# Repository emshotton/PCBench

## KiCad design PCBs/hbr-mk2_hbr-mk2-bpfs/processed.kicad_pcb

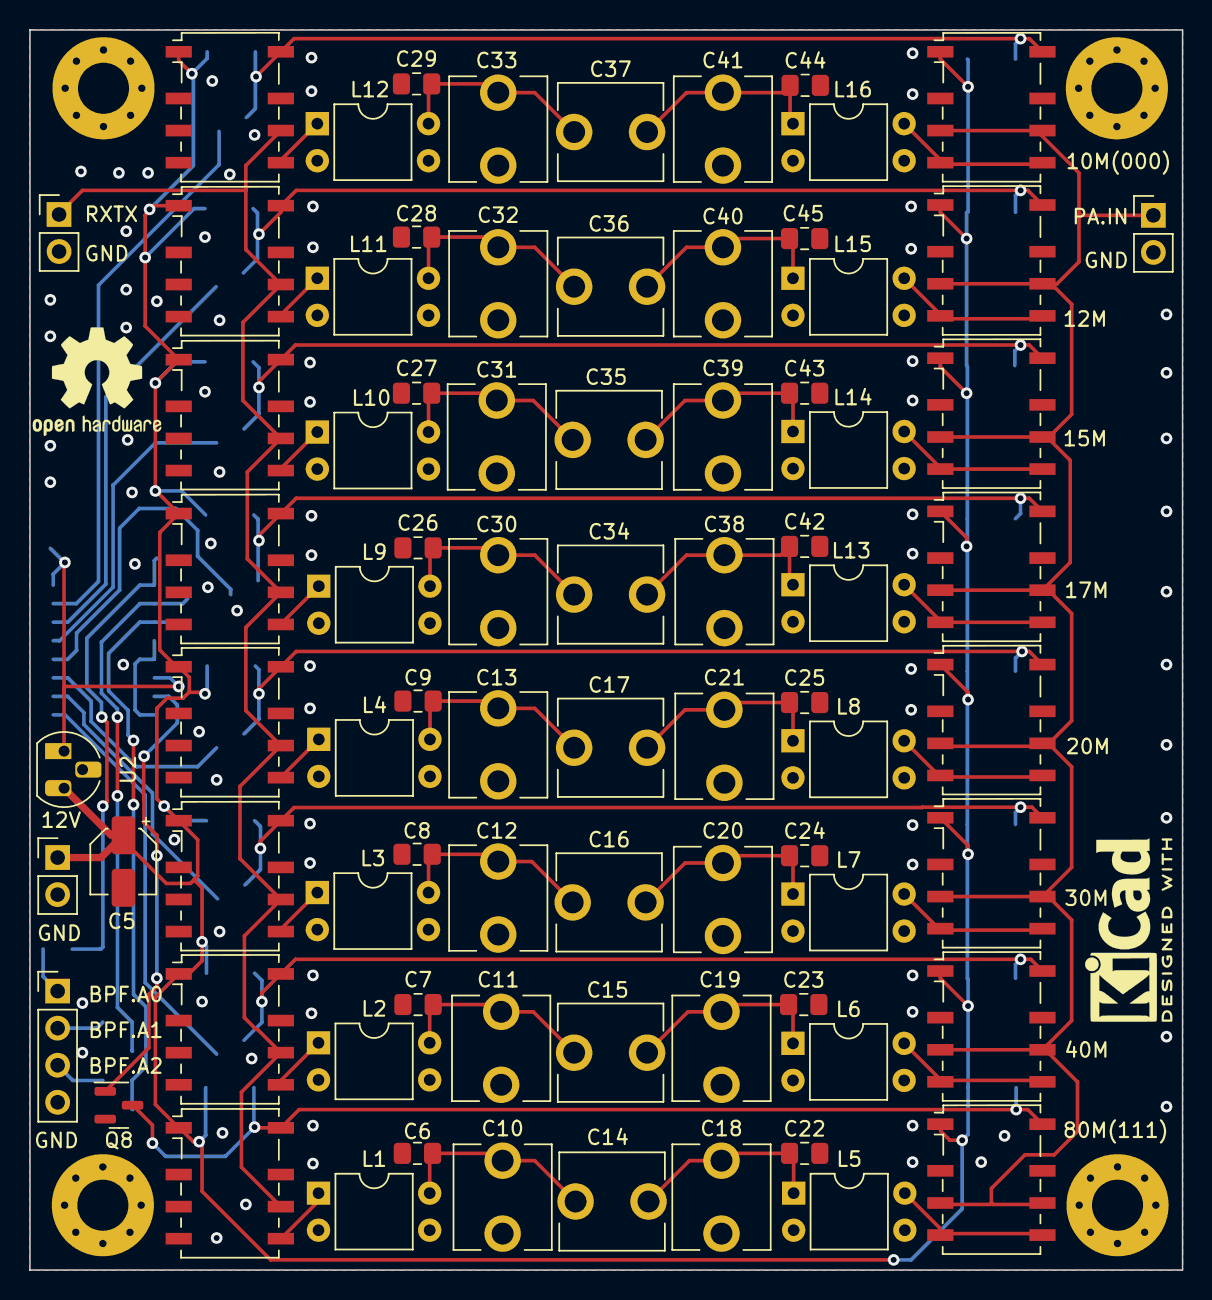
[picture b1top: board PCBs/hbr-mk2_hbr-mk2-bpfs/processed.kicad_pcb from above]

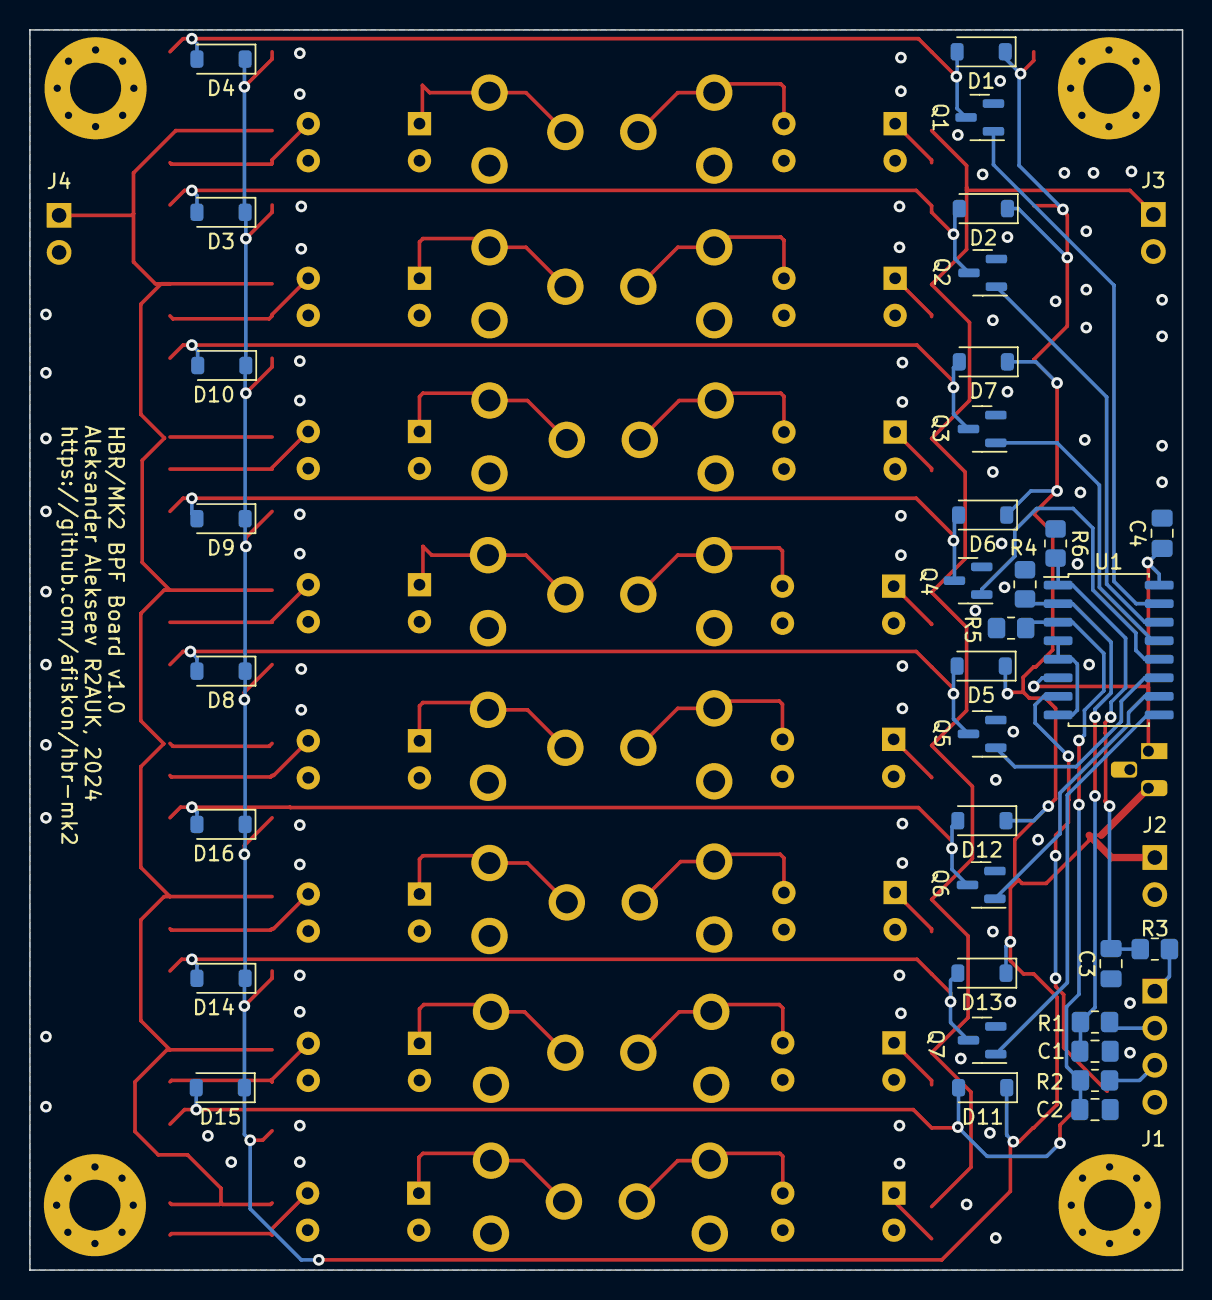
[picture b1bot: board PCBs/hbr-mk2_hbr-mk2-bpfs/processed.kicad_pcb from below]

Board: 2 copper layers, 79.0 x 85.0 mm, 119 parts (34 on the bottom side), 59 nets.

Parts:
C1, C2, C3, C4: 0.1u; C_0805_2012Metric_Pad1.18x1.45mm_HandSolder
C5: 10u; CP_Elec_4x5.4
C6, C22: 470p; C_0805_2012Metric_Pad1.18x1.45mm_HandSolder
C7, C23: 150p; C_0805_2012Metric_Pad1.18x1.45mm_HandSolder
C8, C24: 100p; C_0805_2012Metric_Pad1.18x1.45mm_HandSolder
C9, C25: 68p; C_0805_2012Metric_Pad1.18x1.45mm_HandSolder
C10, C11, C12, C13, C18, C19, C20, C21, C30, C31, C32, C33, C38, C39, C40, C41: 30p; C_Trim_THD_L7.0mm_W6.5mm_P5.00mm
C14: 50p; C_Trim_THD_L7.0mm_W6.5mm_P5.00mm
C15: 20p; C_Trim_THD_L7.0mm_W6.5mm_P5.00mm
C16, C17, C34: 10p; C_Trim_THD_L7.0mm_W6.5mm_P5.00mm
C26, C42: 47p; C_0805_2012Metric_Pad1.18x1.45mm_HandSolder
C27, C43: 33p; C_0805_2012Metric_Pad1.18x1.45mm_HandSolder
C28, C45: 22p; C_0805_2012Metric_Pad1.18x1.45mm_HandSolder
C29, C44: DNP; C_0805_2012Metric_Pad1.18x1.45mm_HandSolder
C35, C36, C37: 5p; C_Trim_THD_L7.0mm_W6.5mm_P5.00mm
D1, D2, D3, D4, D5, D6, D7, D8, D9, D10, D11, D12, D13, D14, D15, D16: 1N4148W; D_SOD-123
H1, H2, H3, H4: MountingHole_Pad; MountingHole_3.5mm_Pad_Via
J1: Conn_01x04; PinHeader_1x04_P2.54mm_Vertical
J2, J3, J4: Conn_01x02; PinHeader_1x02_P2.54mm_Vertical
K1, K2, K3, K4, K5, K6, K7, K8, K9, K10, K11, K12, K13, K14, K15, K16: G6K-2F-Y; Relay_DPDT_Omron_G6K-2F-Y
L1, L5: T37-2; DIP-4_W7.62mm
L2, L3, L4, L6, L7, L8, L9, L10, L11, L12, L13, L14, L15, L16: T37-6; DIP-4_W7.62mm
Q1, Q2, Q3, Q4, Q5, Q6, Q7, Q8: 2N7002; SOT-23
R1, R2, R3: 22; R_0805_2012Metric_Pad1.20x1.40mm_HandSolder
R4, R5, R6: 10K; R_0805_2012Metric_Pad1.20x1.40mm_HandSolder
SYM1: Logo_Open_Hardware_Small; OSHW-Logo2_9.8x8mm_SilkScreen
SYM2: SYM_Radio_Waves_Large; KiCad-Logo2_5mm_SilkScreen
U1: 74HC238; SO-16_5.3x10.2mm_P1.27mm
U2: L78L33_TO92; TO-92_HandSolder

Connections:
+12V: C5.1, D1.1 (K), D2.1 (K), D3.1 (K), D4.1 (K), D5.1 (K), D6.1 (K), D7.1 (K), D8.1 (K), D9.1 (K), D10.1 (K), D11.1 (K), D12.1 (K), D13.1 (K), D14.1 (K), D15.1 (K), D16.1 (K), J2.1, K1.1, K2.1, K3.1, K4.1, K5.1, K6.1, K7.1, K8.1, K9.1, K10.1, K11.1, K12.1, K13.1, K14.1, K15.1, K16.1, U2.3 (VI)
BPFS_IN: J3.1, K1.6, K2.6, K5.6, K6.6, K7.6, K11.6, K12.6, K13.6
BPFS_OUT: J4.1, K3.3, K3.6, K4.3, K4.6, K8.3, K8.6, K9.3, K9.6, K10.3, K10.6, K14.3, K14.6, K15.3, K15.6, K16.3, K16.6
BPF_10_GND: D1.2 (A), D4.2 (A), K2.8, K4.8, Q1.3 (D)
BPF_10_IN: K2.5, L12.1
BPF_10_OUT: K4.4, K4.5, L16.4
BPF_12_GND: D2.2 (A), D3.2 (A), K1.8, K3.8, Q2.3 (D)
BPF_12_IN: K1.5, L11.1
BPF_12_OUT: K3.4, K3.5, L15.4
BPF_15_GND: D7.2 (A), D10.2 (A), K7.8, K10.8, Q3.3 (D)
BPF_15_IN: K7.5, L10.1
BPF_15_OUT: K10.4, K10.5, L14.4
BPF_17_GND: D6.2 (A), D9.2 (A), K6.8, K9.8, Q4.3 (D)
BPF_17_IN: K6.5, L9.1
BPF_17_OUT: K9.4, K9.5, L13.4
BPF_20_GND: D5.2 (A), D8.2 (A), K5.8, K8.8, Q5.3 (D)
BPF_20_IN: K5.5, L4.1
BPF_20_OUT: K8.4, K8.5, L8.4
BPF_30_GND: D12.2 (A), D16.2 (A), K12.8, K15.8, Q6.3 (D)
BPF_30_IN: K12.5, L3.1
BPF_30_OUT: K15.4, K15.5, L7.4
BPF_40_GND: D13.2 (A), D14.2 (A), K13.8, K16.8, Q7.3 (D)
BPF_40_IN: K13.5, L2.1
BPF_40_OUT: K16.4, K16.5, L6.4
BPF_80_GND: D11.2 (A), D15.2 (A), K11.8, K14.8, Q8.3 (D)
BPF_80_IN: K11.5, L1.1
BPF_80_OUT: K14.4, K14.5, L5.4
BPF_SEL_A0: C3.2, R3.1, R6.2, U1.1 (A0)
BPF_SEL_A1: C1.2, R1.1, R4.2, U1.2 (A1)
BPF_SEL_A2: C2.2, R2.1, R5.2, U1.3 (A2)
GND: C1.1, C2.1, C3.1, C4.1, C5.2, C6.2, C7.2, C8.2, C9.2, C10.2, C11.2, C12.2, C13.2, C18.2, C19.2, C20.2, C21.2, C22.2, C23.2, C24.2, C25.2, C26.2, C27.2, C28.2, C29.2, C30.2, C31.2, C32.2, C33.2, C38.2, C39.2, C40.2, C41.2, C42.2, C43.2, C44.2, C45.2, H1.1, H2.1, H3.1, H4.1, J1.4, J2.2, J3.2, J4.2, K1.2, K1.3, K1.4, K2.2, K2.3, K2.4, K5.2, K5.3, K5.4, K6.2, K6.3, K6.4, K7.2, K7.3, K7.4, K11.2, K11.3, K11.4, K12.2, K12.3, K12.4, K13.2, K13.3, K13.4, L1.2, L1.3, L2.2, L2.3, L3.2, L3.3, L4.2, L4.3, L5.2, L5.3, L6.2, L6.3, L7.2, L7.3, L8.2, L8.3, L9.2, L9.3, L10.2, L10.3, L11.2, L11.3, L12.2, L12.3, L13.2, L13.3, L14.2, L14.3, L15.2, L15.3, L16.2, L16.3, Q1.2 (S), Q2.2 (S), Q3.2 (S), Q4.2 (S), Q5.2 (S), Q6.2 (S), Q7.2 (S), Q8.2 (S), R4.1, R5.1, R6.1, U1.4 (~E1), U1.5 (~E2), U1.8 (GND), U2.2 (GND)
unnamed: C6.1, C10.1, C14.2, L1.4
unnamed: C7.1, C11.1, C15.2, L2.4
unnamed: C8.1, C12.1, C16.2, L3.4
unnamed: C9.1, C13.1, C17.2, L4.4
unnamed: C14.1, C18.1, C22.1, L5.1
unnamed: C15.1, C19.1, C23.1, L6.1
unnamed: C16.1, C20.1, C24.1, L7.1
unnamed: C17.1, C21.1, C25.1, L8.1
unnamed: C26.1, C30.1, C34.2, L9.4
unnamed: C27.1, C31.1, C35.2, L10.4
unnamed: C28.1, C32.1, C36.2, L11.4
unnamed: C29.1, C33.1, C37.2, L12.4
unnamed: C34.1, C38.1, C42.1, L13.1
unnamed: C35.1, C39.1, C43.1, L14.1
unnamed: C36.1, C40.1, C45.1, L15.1
unnamed: C37.1, C41.1, C44.1, L16.1
unnamed: J1.1, R3.2
unnamed: J1.2, R1.2
unnamed: J1.3, R2.2
unnamed: Q1.1 (G), U1.15 (Y0)
unnamed: Q2.1 (G), U1.14 (Y1)
unnamed: Q3.1 (G), U1.13 (Y2)
unnamed: Q4.1 (G), U1.12 (Y3)
unnamed: Q5.1 (G), U1.11 (Y4)
unnamed: Q6.1 (G), U1.10 (Y5)
unnamed: Q7.1 (G), U1.9 (Y6)
unnamed: Q8.1 (G), U1.7 (Y7)
unnamed: C4.2, U1.6 (E3), U1.16 (VCC), U2.1 (VO)

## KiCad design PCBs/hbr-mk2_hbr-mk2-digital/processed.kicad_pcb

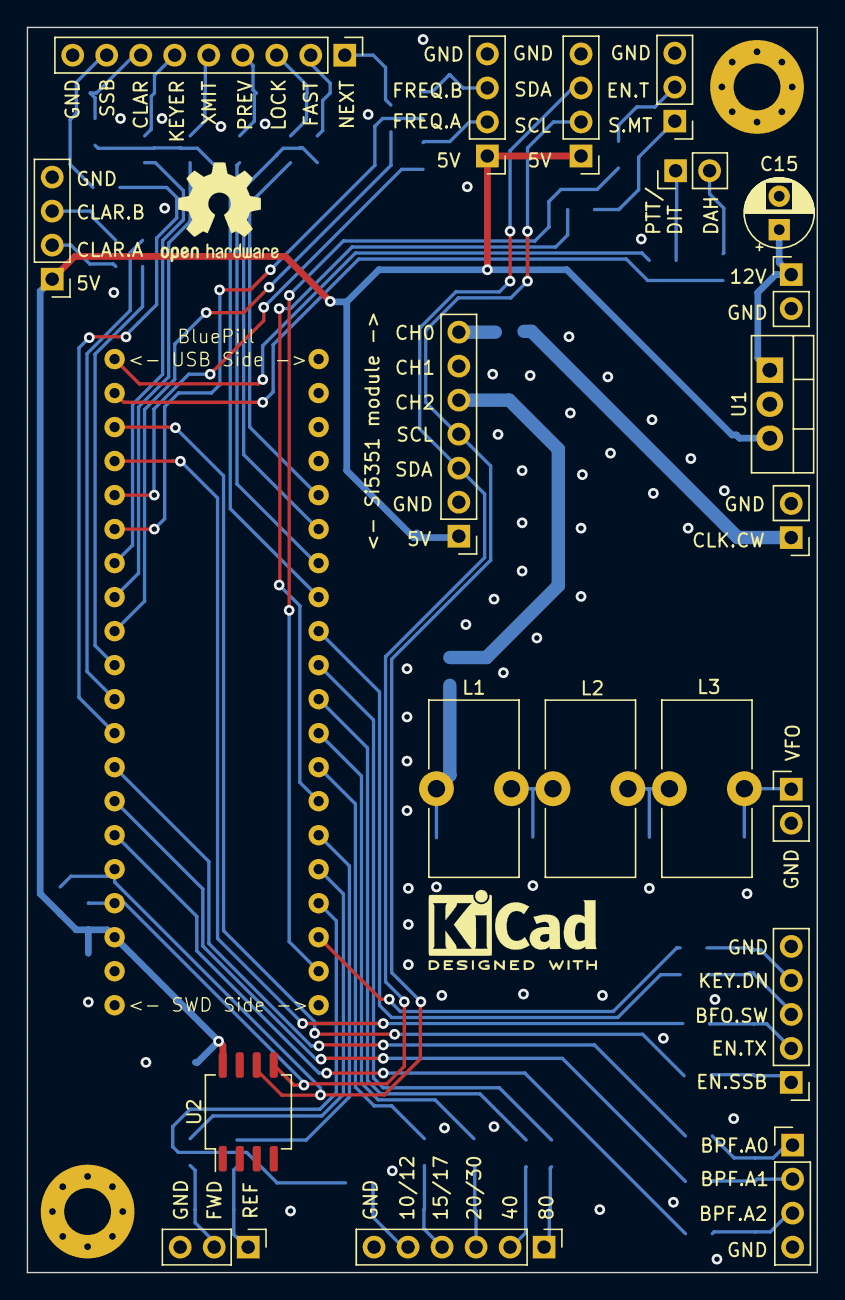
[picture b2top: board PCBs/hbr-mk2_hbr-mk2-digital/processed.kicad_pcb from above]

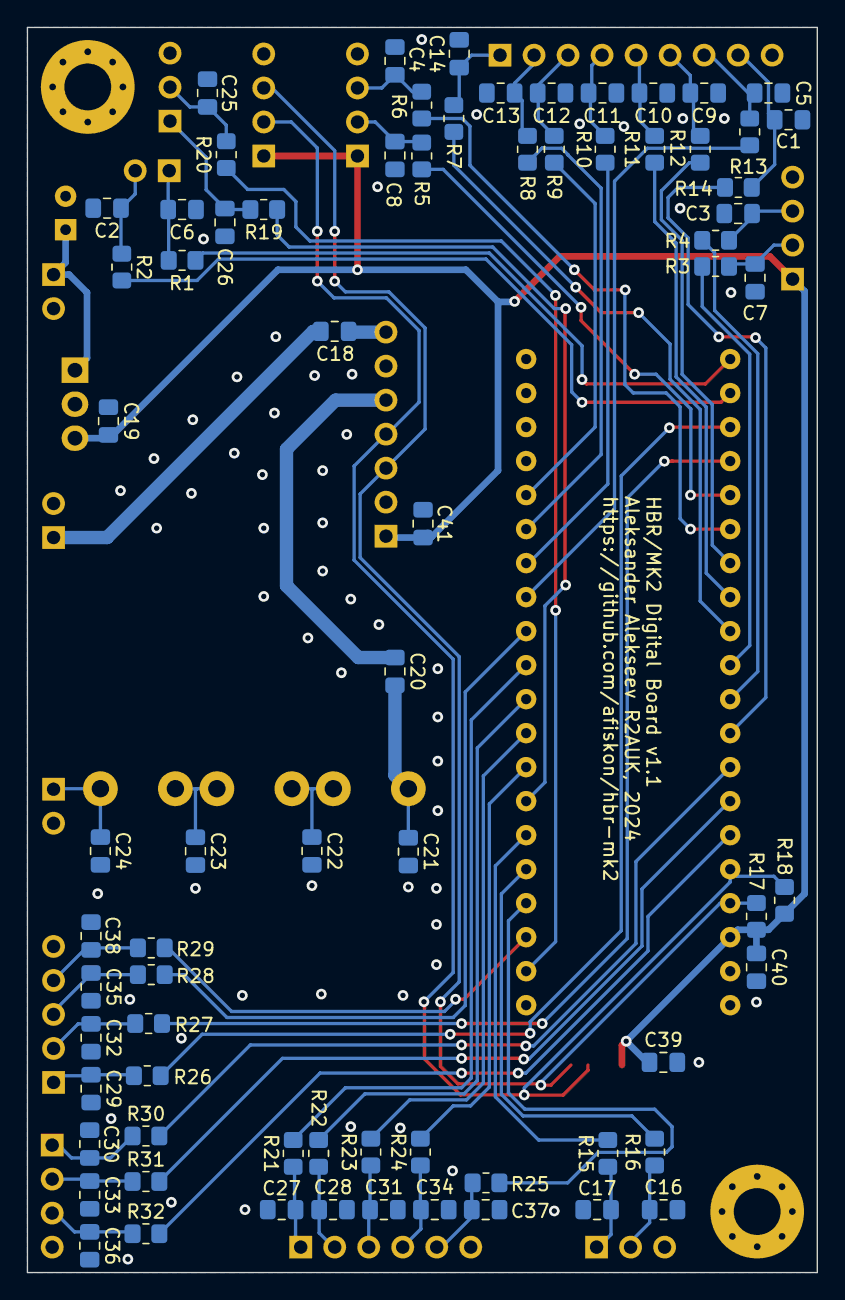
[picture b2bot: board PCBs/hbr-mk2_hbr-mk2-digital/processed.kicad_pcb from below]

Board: 2 copper layers, 59.0 x 93.0 mm, 97 parts (72 on the bottom side), 72 nets.

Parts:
C1, C2, C3, C4, C5, C6, C7, C8, C9, C10, C11, C12, C13, C14, C16, C17, C18, C19, C20, C25, C26, C27, C28, C29, C30, C31, C32, C33, C34, C35, C36, C37, C38, C39, C40, C41: 0.1u; C_0805_2012Metric_Pad1.18x1.45mm_HandSolder
C15: 10u; CP_Radial_D5.0mm_P2.50mm
C21, C24: 120p; C_0805_2012Metric_Pad1.18x1.45mm_HandSolder
C22, C23: 180p; C_0805_2012Metric_Pad1.18x1.45mm_HandSolder
H1, H2: MountingHole_Pad; MountingHole_3.5mm_Pad_Via
J1: Conn_01x09; PinHeader_1x09_P2.54mm_Vertical
J2, J12, J13, J14: Conn_01x02; PinHeader_1x02_P2.54mm_Vertical
J3, J4, J8, J9: Conn_01x04; PinHeader_1x04_P2.54mm_Vertical
J5, J7: Conn_01x03; PinHeader_1x03_P2.54mm_Vertical
J6: Conn_01x07; PinHeader_1x07_P2.54mm_Vertical
J10: Conn_01x06; PinHeader_1x06_P2.54mm_Vertical
J11: Conn_01x05; PinHeader_1x05_P2.54mm_Vertical
L1, L2, L3: T50-6; L_Toroid_Vertical_L13.0mm_W6.5mm_P5.60mm
R1, R2, R3, R4, R5, R6, R7, R8, R9, R10, R11, R12, R13, R14, R15, R16, R19, R20, R21, R22, R23, R24, R25, R26, R27, R28, R29, R30, R31, R32: 22; R_0805_2012Metric_Pad1.20x1.40mm_HandSolder
R17, R18: 4.7K; R_0805_2012Metric_Pad1.20x1.40mm_HandSolder
SYM1: Logo_Open_Hardware_Small; OSHW-Logo2_9.8x8mm_SilkScreen
SYM2: SYM_Radio_Waves_Large; KiCad-Logo2_5mm_SilkScreen
U1: LM7805; TO-220-3_Vertical
U2: 24LC64; SO-8_5.3x6.2mm_P1.27mm
U3: BluePill

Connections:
+5VD: C19.1, C39.1, C40.1, C41.1, J3.1, J4.1, J6.1, J8.1, R17.1, R18.1, U1.3 (VO), U2.8 (VCC), U3.18 (5V)
+12V: C15.1, J14.1, U1.1 (VI)
BFO_SWITCH: R28.2, U3.32 (A7)
BPF_SEL_A0: R30.2, U3.13 (B5)
BPF_SEL_A1: R31.2, U3.14 (B6)
BPF_SEL_A2: R32.2, U3.15 (B7)
BTN_CLAR: R13.2, U3.33 (B0)
BTN_FAST: R8.2, U3.35 (B10)
BTN_KEYER: R12.2, U3.7 (A10)
BTN_LOCK: R9.2, U3.36 (B11)
BTN_NEXT: R7.2, U3.9 (A12)
BTN_PREV: R10.2, U3.34 (B1)
BTN_XMIT: R11.2, U3.8 (A11)
CLAR_ROT_A: R3.2, U3.10 (A15)
CLAR_ROT_B: R4.2, U3.11 (B3)
CLK_CW: C18.2, J13.1
ENABLE_CW_TONE: R20.2, U3.22 (C13)
ENABLE_KEYED_VCC: R29.2, U3.23 (C14)
ENABLE_SSB_MODE: R26.2, U3.3 (B14)
ENABLE_TX_12V: R27.2, U3.4 (B15)
FREQ_ROT_A: R5.2, U3.5 (A8)
FREQ_ROT_B: R6.2, U3.6 (A9)
GND: C1.2, C2.2, C3.2, C4.2, C5.2, C6.2, C7.2, C8.2, C9.2, C10.2, C11.2, C12.2, C13.2, C14.2, C15.2, C16.2, C17.2, C19.2, C21.2, C22.2, C23.2, C24.2, C25.2, C26.2, C27.2, C28.2, C29.2, C30.2, C31.2, C32.2, C33.2, C34.2, C35.2, C36.2, C37.2, C38.2, C39.2, C40.2, C41.2, H1.1, H2.1, J1.9, J3.4, J4.4, J5.3, J6.2, J7.3, J8.4, J9.4, J10.6, J11.5, J12.2, J13.2, J14.2, U1.2 (GND), U2.1 (A0), U2.2 (A1), U2.3 (A2), U2.4 (GND), U2.7 (WP), U3.19 (GND1), U3.39 (GND2), U3.40 (GND3)
I2C_SCL: J6.4, J8.2, R18.2, U2.6 (SCL), U3.16 (B8)
I2C_SDA: J6.3, J8.3, R17.2, U2.5 (SDA), U3.17 (B9)
KEY_DAH: R2.2, U3.2 (B13)
KEY_DIT_AND_PTT: R1.2, U3.1 (B12)
LPF_SEL_10_12: R25.2, U3.24 (C15)
LPF_SEL_15_17: R24.2, U3.28 (A3)
LPF_SEL_20_30: R23.2, U3.29 (A4)
LPF_SEL_40: R22.2, U3.30 (A5)
LPF_SEL_80: R21.2, U3.31 (A6)
unnamed: C20.2, C21.1, L1.1
unnamed: C22.1, L1.2, L2.1
unnamed: C23.1, L2.2, L3.1
unnamed: C14.1, J1.1, R7.1
unnamed: C13.1, J1.2, R8.1
unnamed: C12.1, J1.3, R9.1
unnamed: C11.1, J1.4, R10.1
unnamed: C10.1, J1.5, R11.1
unnamed: C9.1, J1.6, R12.1
unnamed: C5.1, J1.7, R13.1
unnamed: C1.1, J1.8, R14.1
unnamed: C6.1, J2.1, R1.1
unnamed: C2.1, J2.2, R2.1
unnamed: C7.1, J3.2, R3.1
unnamed: C3.1, J3.3, R4.1
unnamed: C8.1, J4.2, R5.1
unnamed: C4.1, J4.3, R6.1
unnamed: C17.1, J5.1, R15.1
unnamed: C16.1, J5.2, R16.1
unnamed: C20.1, J6.5
unnamed: C18.1, J6.7
unnamed: C26.1, J7.1, R19.1
unnamed: C25.1, J7.2, R20.1
unnamed: C30.1, J9.1, R30.1
unnamed: C33.1, J9.2, R31.1
unnamed: C36.1, J9.3, R32.1
unnamed: C27.1, J10.1, R21.1
unnamed: C28.1, J10.2, R22.1
unnamed: C31.1, J10.3, R23.1
unnamed: C34.1, J10.4, R24.1
unnamed: C37.1, J10.5, R25.1
unnamed: C29.1, J11.1, R26.1
unnamed: C32.1, J11.2, R27.1
unnamed: C35.1, J11.3, R28.1
unnamed: C38.1, J11.4, R29.1
PWR_FWD: R16.2, U3.25 (A0)
PWR_REF: R15.2, U3.26 (A1)
SSB_GND: R14.2, U3.12 (B4)
S_METER_OUT: R19.2, U3.27 (A2)
VFO: C24.1, J12.1, L3.2

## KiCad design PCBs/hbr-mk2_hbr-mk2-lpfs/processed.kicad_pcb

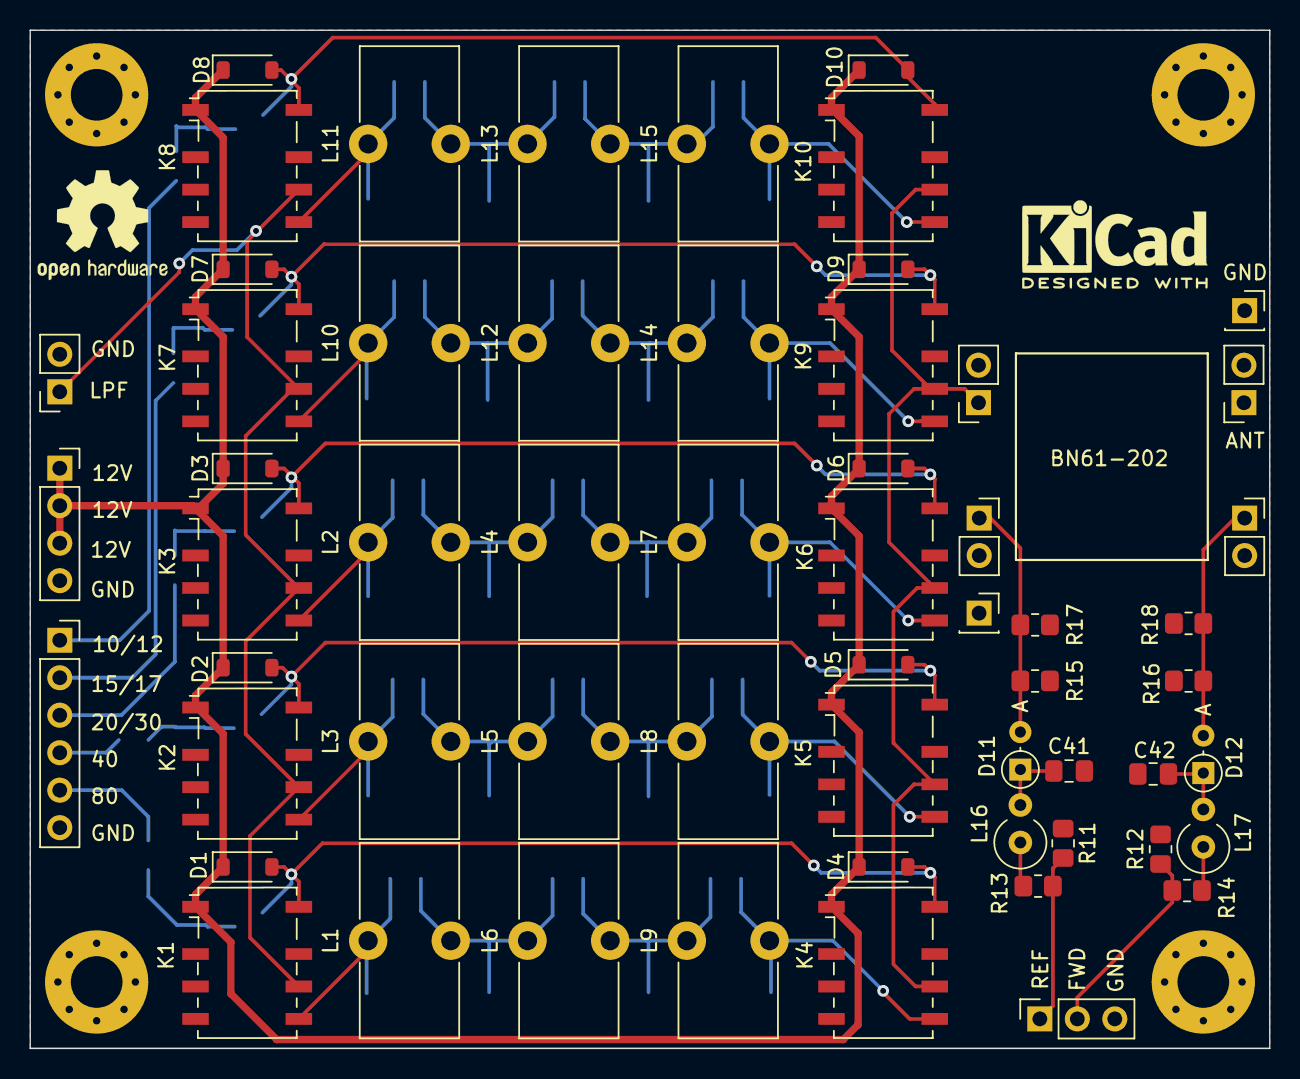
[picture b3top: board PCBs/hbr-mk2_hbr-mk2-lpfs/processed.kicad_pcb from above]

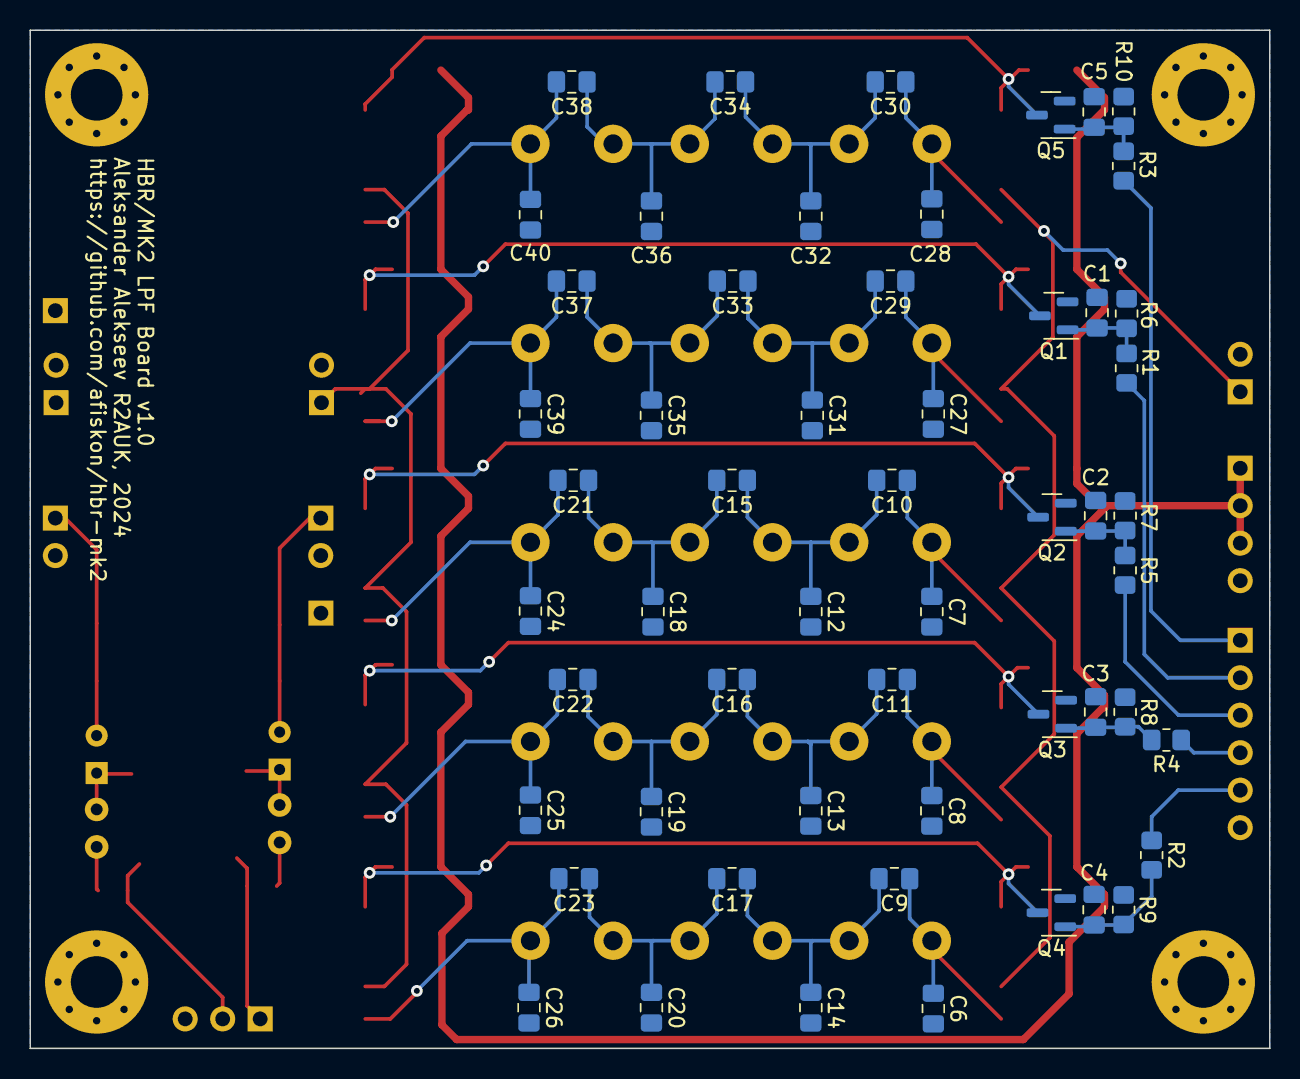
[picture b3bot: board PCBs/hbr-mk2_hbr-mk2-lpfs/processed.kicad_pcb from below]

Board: 2 copper layers, 84.0 x 69.0 mm, 120 parts (55 on the bottom side), 47 nets.

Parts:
C1, C2, C3, C4, C5: 0.1u; C_0805_2012Metric_Pad1.18x1.45mm_HandSolder
C6, C20: 680p; C_0805_2012Metric_Pad1.18x1.45mm_HandSolder
C7, C16, C18, C22, C25, C31: 220p; C_0805_2012Metric_Pad1.18x1.45mm_HandSolder
C8, C12, C23: 330p; C_0805_2012Metric_Pad1.18x1.45mm_HandSolder
C9, C21, C28, C33, C36, C39: 100p; C_0805_2012Metric_Pad1.18x1.45mm_HandSolder
C10: 33p; C_0805_2012Metric_Pad1.18x1.45mm_HandSolder
C11, C38: 47p; C_0805_2012Metric_Pad1.18x1.45mm_HandSolder
C13, C17, C19, C26: 470p; C_0805_2012Metric_Pad1.18x1.45mm_HandSolder
C14: 820p; C_0805_2012Metric_Pad1.18x1.45mm_HandSolder
C15, C24, C27, C32, C35: 150p; C_0805_2012Metric_Pad1.18x1.45mm_HandSolder
C29: 22p; C_0805_2012Metric_Pad1.18x1.45mm_HandSolder
C30: 18p; C_0805_2012Metric_Pad1.18x1.45mm_HandSolder
C34, C37, C40: 68p; C_0805_2012Metric_Pad1.18x1.45mm_HandSolder
C41, C42: 0.01u; C_0805_2012Metric_Pad1.18x1.45mm_HandSolder
D1, D2, D3, D4, D5, D6, D7, D8, D9, D10: 1N4148W; D_SOD-123
D11, D12: 1N34 / D311 (*); D_DO-34_SOD68_P2.54mm_Vertical_AnodeUp
H1, H2, H3, H4: MountingHole_Pad; MountingHole_3.5mm_Pad_Via
J1: Conn_01x03; PinSocket_1x03_P2.54mm_Vertical
J2: Conn_01x02; PinSocket_1x02_P2.54mm_Vertical
J3: Conn_01x06; PinSocket_1x06_P2.54mm_Vertical
J4: Conn_01x04; PinSocket_1x04_P2.54mm_Vertical
J6, J7, J8, J9: Conn_Coaxial; PinSocket_1x02_P2.54mm_Vertical
J10, J11: Conn_01x01; PinSocket_1x01_P2.54mm_Vertical
K1, K2, K3, K4, K5, K6, K7, K8, K9, K10: G6K-2F-Y; Relay_DPDT_Omron_G6K-2F-Y
L1, L2, L3, L4, L5, L6, L7, L8, L9, L10, L11, L12, L13, L14, L15: T50-6; L_Toroid_Vertical_L13.0mm_W6.5mm_P5.60mm
L16, L17: 1 mH; L_Axial_L7.0mm_D3.3mm_P2.54mm_Vertical_Fastron_MICC
Q1, Q2, Q3, Q4, Q5: 2N7002; SOT-23
R1, R2, R3, R4, R5: 22; R_0805_2012Metric_Pad1.20x1.40mm_HandSolder
R6, R7, R8, R9, R10: 10K; R_0805_2012Metric_Pad1.20x1.40mm_HandSolder
R11, R12: 1K; R_0805_2012Metric_Pad1.20x1.40mm_HandSolder
R13, R14: 220; R_0805_2012Metric_Pad1.20x1.40mm_HandSolder
R15, R16, R17, R18: 100; R_0805_2012Metric_Pad1.20x1.40mm_HandSolder
SYM1: Logo_Open_Hardware_Small; OSHW-Logo2_9.8x8mm_SilkScreen
SYM2: SYM_Radio_Waves_Large; KiCad-Logo2_5mm_SilkScreen

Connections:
+12V: D1.1 (K), D2.1 (K), D3.1 (K), D4.1 (K), D5.1 (K), D6.1 (K), D7.1 (K), D8.1 (K), D9.1 (K), D10.1 (K), J4.1, J4.2, J4.3, K1.1, K2.1, K3.1, K4.1, K5.1, K6.1, K7.1, K8.1, K9.1, K10.1
GND: C1.2, C2.2, C3.2, C4.2, C5.2, C6.2, C7.2, C8.2, C12.2, C13.2, C14.2, C18.2, C19.2, C20.2, C24.2, C25.2, C26.2, C27.2, C28.2, C31.2, C32.2, C35.2, C36.2, C39.2, C40.2, C41.2, C42.2, H1.1, H2.1, H3.1, H4.1, J1.3, J2.2, J3.6, J4.4, J6.2 (Ext), J9.2 (Ext), J10.1, J11.1, K1.2, K1.3, K1.4, K2.2, K2.3, K2.4, K3.2, K3.3, K3.4, K4.2, K4.3, K4.4, K5.2, K5.3, K5.4, K6.2, K6.3, K6.4, K7.2, K7.3, K7.4, K8.2, K8.3, K8.4, K9.2, K9.3, K9.4, K10.2, K10.3, K10.4, Q1.2 (S), Q2.2 (S), Q3.2 (S), Q4.2 (S), Q5.2 (S), R6.2, R7.2, R8.2, R9.2, R10.2, R11.1, R12.1, R15.2, R16.2, R17.2, R18.2
LPFS_IN: J6.1 (In), K4.6, K5.6, K6.6, K9.6, K10.6
LPFS_OUT: J2.1, K1.6, K2.6, K3.6, K7.6, K8.6
LPF_10_12_GND: D8.2 (A), D10.2 (A), K8.8, K10.8, Q5.3 (D)
LPF_15_17_GND: D7.2 (A), D9.2 (A), K7.8, K9.8, Q1.3 (D)
LPF_20_30_GND: D3.2 (A), D6.2 (A), K3.8, K6.8, Q2.3 (D)
LPF_40_GND: D2.2 (A), D5.2 (A), K2.8, K5.8, Q3.3 (D)
LPF_80_GND: D1.2 (A), D4.2 (A), K1.8, K4.8, Q4.3 (D)
LPF_SEL_10_12: J3.1, R3.1
LPF_SEL_15_17: J3.2, R1.1
LPF_SEL_20_30: J3.3, R5.1
LPF_SEL_40: J3.4, R4.1
LPF_SEL_80: J3.5, R2.1
unnamed: C6.1, C9.1, K1.5, L1.1
unnamed: C7.1, C10.1, K3.5, L2.1
unnamed: C10.2, C12.1, C15.1, L2.2, L4.1
unnamed: C8.1, C11.1, K2.5, L3.1
unnamed: C11.2, C13.1, C16.1, L3.2, L5.1
unnamed: C9.2, C14.1, C17.1, L1.2, L6.1
unnamed: C15.2, C18.1, C21.1, L4.2, L7.1
unnamed: C16.2, C19.1, C22.1, L5.2, L8.1
unnamed: C17.2, C20.1, C23.1, L6.2, L9.1
unnamed: C21.2, C24.1, K6.5, L7.2
unnamed: C22.2, C25.1, K5.5, L8.2
unnamed: C23.2, C26.1, K4.5, L9.2
unnamed: C27.1, C29.1, K7.5, L10.1
unnamed: C28.1, C30.1, K8.5, L11.1
unnamed: C29.2, C31.1, C33.1, L10.2, L12.1
unnamed: C30.2, C32.1, C34.1, L11.2, L13.1
unnamed: C33.2, C35.1, C37.1, L12.2, L14.1
unnamed: C34.2, C36.1, C38.1, L13.2, L15.1
unnamed: C37.2, C39.1, K9.5, L14.2
unnamed: C38.2, C40.1, K10.5, L15.2
unnamed: D11.2 (A), J7.1 (In), R15.1, R17.1
unnamed: C41.1, D11.1 (K), L16.2
unnamed: D12.2 (A), J9.1 (In), R16.1, R18.1
unnamed: C42.1, D12.1 (K), L17.2
unnamed: L16.1, R13.2
unnamed: L17.1, R14.2
unnamed: C1.1, Q1.1 (G), R1.2, R6.1
unnamed: C2.1, Q2.1 (G), R5.2, R7.1
unnamed: C3.1, Q3.1 (G), R4.2, R8.1
unnamed: C4.1, Q4.1 (G), R2.2, R9.1
unnamed: C5.1, Q5.1 (G), R3.2, R10.1
PWR_FWD: J1.2, R12.2, R14.1
PWR_REF: J1.1, R11.2, R13.1

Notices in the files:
PCBs/icezum_icezum/processed.kicad_pcb:
License: Creative commons Attribution ShareAlike
